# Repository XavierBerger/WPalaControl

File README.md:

# WPalaControl

**WPalaControl** is a device designed to control and monitor Fumis-based stoves using a D1 Mini.  
It allows you to power on/off, adjust the set point, change fan speeds, and retrieve status, alarms, and temperature data from your stove.  

It supports native HTTP requests which makes it fully compatible with all existing Palazzetti/Fumis home automation plugins/apps.  

It also integrates with MQTT to monitor/control your stove in a much more efficient way.  

## Stove Compatibility

WPalaControl is compatible with stoves using the Fumis Controller, which is used by many manufacturers, including:  
  
Palazzetti / Jotul / TurboFonte / Godin / Fonte Flamme / Invicta / Casatelli / Alpis / Faizen / HETA / ...

To determine if your stove is compatible with WPalaControl, look for the following Control Panel or Motherboard:  

## Home Automation compatibility

|  | [MQTT Integration](https://www.home-assistant.io/integrations/mqtt/) (autodiscovery) <br> Most options and fans control |  |
| ------------- | ------------- | ------------- |
|  | [Palazzetti Integration](https://www.home-assistant.io/integrations/palazzetti)<br> (2024.11 minimum) <br> Basic implementation for now |  |
|  | [Palazzetti plugin](https://www.jeedom.com/market/index.php?v=d&p=market_display&id=3104) |  |

## Make/Get your adapter

🔧 If you want to build it yourself, you can find all details here : [BUILD](BUILD.md) 🔧  

🛍️🚀 Otherwise, I'm producing some small batches and offering it ready-to-use here :  

## Connect

⚠️ **Before connecting, please check that you are using the correct cable**  
For Hardware V1.x: please use a **Crossed** cable  
For Hardware V2.x: please use a **Straight** cable  
_(Hardware version is written on the box and on the PCB)_

✅If your stove has an accessible RJ12 connector, simply connect the cable.  

🔍If not, you'll need an additional cable and a splitter.  
➡️ More details can be found in the [Splitter Cabling documentation](SPLITTERCABLING.md)

## First Boot

During the first Boot, the WPalaControl creates its own Wi-Fi network (AP mode)  

Firmware version **3.2.0 and higher**:  

- Network SSID : `WPalaControl`
- Password : `password`

Version **3.1.x and lower**:  

- Network SSID : `WirelessPalaControlXXXX`
- Password : `PasswordPalaControl`

You should be automatically redirected to the module page.  
If not, go to 👉 <http://wpalacontrol.local> 👈

## Configuration pages

### Status

Provides useful informations about the module and the stove.  
**The stove SN appears then followed, 1 minute later, by refreshed stove information**  

### Config

#### System

- **Reboot**: restart the module
- **Reboot in Rescue Mode**: restart the module with default configuration

#### WiFi

- **ssid & password**: IDs of your Wifi Network  
- **hostname**: name of ESP on the network  
- **IP, GW, NetMask, DNS1&2**: Fixed IP configuration  

#### PalaControl - Home Automation

- **Type**: enable/disable MQTT communication  
- **Upload Period**: set the refresh interval of stove information (in seconds)  
- **Hostname, Port, Username, Password**: MQTT server details (username and password are - optional)  
- **Base Topic**: prefix for WPalaControl topic structure  
- **MQTT Type**: defines MQTT topics and data structure:  
  - **Generic**: publish raw values under the base topic (e.g. "{baseTopic}/T1" = "*20.00*")
  - **Generic JSON**: publish values JSON to "category" topic under base topic (e.g. "{baseTopic}/TMPS" = "*{"INFO":{"CMD":"GET TMPS","RSP":"OK......*")
  - **Generic Categorized**: publish raw values to "category" topic under base topic (e.g. "{baseTopic}/TMPS/T1" = "*20.00*")
- **Home Assistant Discovery**: Enable/disable Home Assistant auto-discovery

### Firmware

Aallows you to flash a new firmware version directly from GitHub releases or using `WPalaControl.*.bin` or `WirelessPalaControl.*.bin` file:  
  
Ensure the module has Internet access and/or DNS configured if IP address is static

## Use it

### HTTP

Natively, HTTP GET request can be sent directly to the module.  

```
http://wpalacontrol.local/cgi-bin/sendmsg.lua?cmd={command}
```

### MQTT

Send commands via MQTT to `%BaseTopic%/cmd` topic once MQTT is configured.  
Execution result is:

- published following the configured MQTT Type
- published on `%BaseTopic%/result` in JSON format

Module connection status is published to `%BaseTopic%/connected`:

- 0: not connected
- 1: connected but no communication with the stove
- 2: module and stove connected

### Command List
  
- `GET+STDT`: get static data
- `GET+ALLS`: get all status data
- `GET+STAT`: get status of the stove⏲️
- `GET+TMPS`: get temperatures of the stove⏲️
- `GET+FAND`: get Fan values⏲️
- `GET+SETP`: get current Set Point (desired temperature)⏲️
- `GET+POWR`: get current power (1-5)⏲️
- `GET+CUNT`: get some counters
- `GET+CNTR`: get some counters (same as GET+CUNT)⏲️
- `GET+DPRS`: get delta pressure data⏲️
- `GET+TIME`: get stove clock data⏲️
- `GET+IOPT`: get IO ports status
- `GET+SERN`: get stove Serial Number
- `GET+MDVE`: get stove model and fw version
- `GET+CHRD`: get chrono data
- `GET+PARM+92`: get parameter (ex : 92=pellet type (1-3))
- `GET+HPAR+57`: get hidden parameter (ex : 57=% of pellet to feed for pellet type 3)
- `BKP+PARM+CSV`: get all parameters in a CSV file (HTTP only) ✨
- `BKP+PARM+JSON`: get all parameters in a JSON file (HTTP only) ✨
- `BKP+HPAR+CSV`: get all hidden parameters in a CSV file (HTTP only) ✨
- `BKP+HPAR+JSON`: get all hidden parameters in a JSON file (HTTP only) ✨
- `CMD+ON`: turn stove ON
- `CMD+OFF`: turn stove OFF
- `SET+POWR+3`: set power (1-5)
- `SET+PWRU`: increase power by 1 unit
- `SET+PWRD`: decrease power by 1 unit
- `SET+SETP+20`: set Set Point (desired temperature)
- `SET+STPF+19.8`: set Set Point with a 0.2° precision (depend of your stove model)✨
- `SET+STPU`: increase Set Point by 1 unit
- `SET+STPD`: decrease Set Point by 1 unit
- `SET+RFAN+7`: set Room Fan value (0-5;6=Max;7=Auto)
- `SET+FN2U`: increase Room Fan by 1 unit
- `SET+FN2D`: decrease Room Fan by 1 unit
- `SET+FN3L+0`: set Room Fan 3 value (0-5)
- `SET+FN4L+0`: set Room Fan 4 value (0-5)
- `SET+SLNT+0`: set Silent mode value (0-1)
- `SET+TIME+2023-12-28+19:42:00`: set stove Date and Time (2000-2099) (1-12) (1-31) (0-23) (0-59) (0-59)
- `SET+CSST+0`: set Chrono Status value (0-1)
- `SET+CSTH+2+18`: set Chrono Program Start Hour (1-6) (0-23)
- `SET+CSTM+2+30`: set Chrono Program Start Minute (1-6) (0-59)
- `SET+CSPH+2+22`: set Chrono Program Stop Hour (1-6) (0-23)
- `SET+CSPM+2+45`: set Chrono Program Stop Minute (1-6) (0-59)
- `SET+CSET+2+19`: set Chrono Program Set Point (1-6) (desired temperature)
- `SET+CDAY+7+3+6`: set Chrono Program for week day (Day-Mem-Prog) (1-7) (1-3) (1-6)
- `SET+CPRD+1+19+18+30+22+45`: set Chrono Program data (Prog-Temp-StartH-StartM-StopH-StopM) (1-6) (temperature) (0-23) (0-59) (0-23) (0-59)
- `SET+PARM+92+2`: set parameter 92 to value 2 (ex : 92=pellet type (1-3))
- `SET+HPAR+57+95`: set hidden parameter 57 to value 95 (ex : 57=% of pellet to feed for pellet type 3)

⏲️: Published automatically  
✨: WPalaControl specific commands

### Description

MQTT infos published every "Upload Period":

- `STATUS`: status of the stove
- `LSTATUS`: status of the stove
- `T1`, `T2`, `T3`, `T4`, `T5`: temperature of the stove
- `F1V`, `F2V`, `F2L`, `F2LF`, `F3L`, `F4L`: fan values (meaning depend of your stove model)
- `IGN`: ignition counter
- `IGNERRORS`: ignition error counter
- `POWERTIME`: total heating time (hour:minute)
- `HEATTIME`: ??? (hour:minute)
- `SERVICETIME`: heating time since last maintenance (hour:minute)
- `ONTIME`: time from last power ON (hour:minute)
- `OVERTMPERRORS`: overtemperature error counter
- `STOVE_DATETIME`: date of the stove
- `STOVE_WDAY`: week day of the stove
- `SETP`: current Set Point (desired temperature)
- `PQT`: wood pellet consumption
- `PWR`: current power (1-5)
- `FDR`: feeder
- `DP_TARGET`: delta pressure target
- `DP_PRESS`: actual delta pressure

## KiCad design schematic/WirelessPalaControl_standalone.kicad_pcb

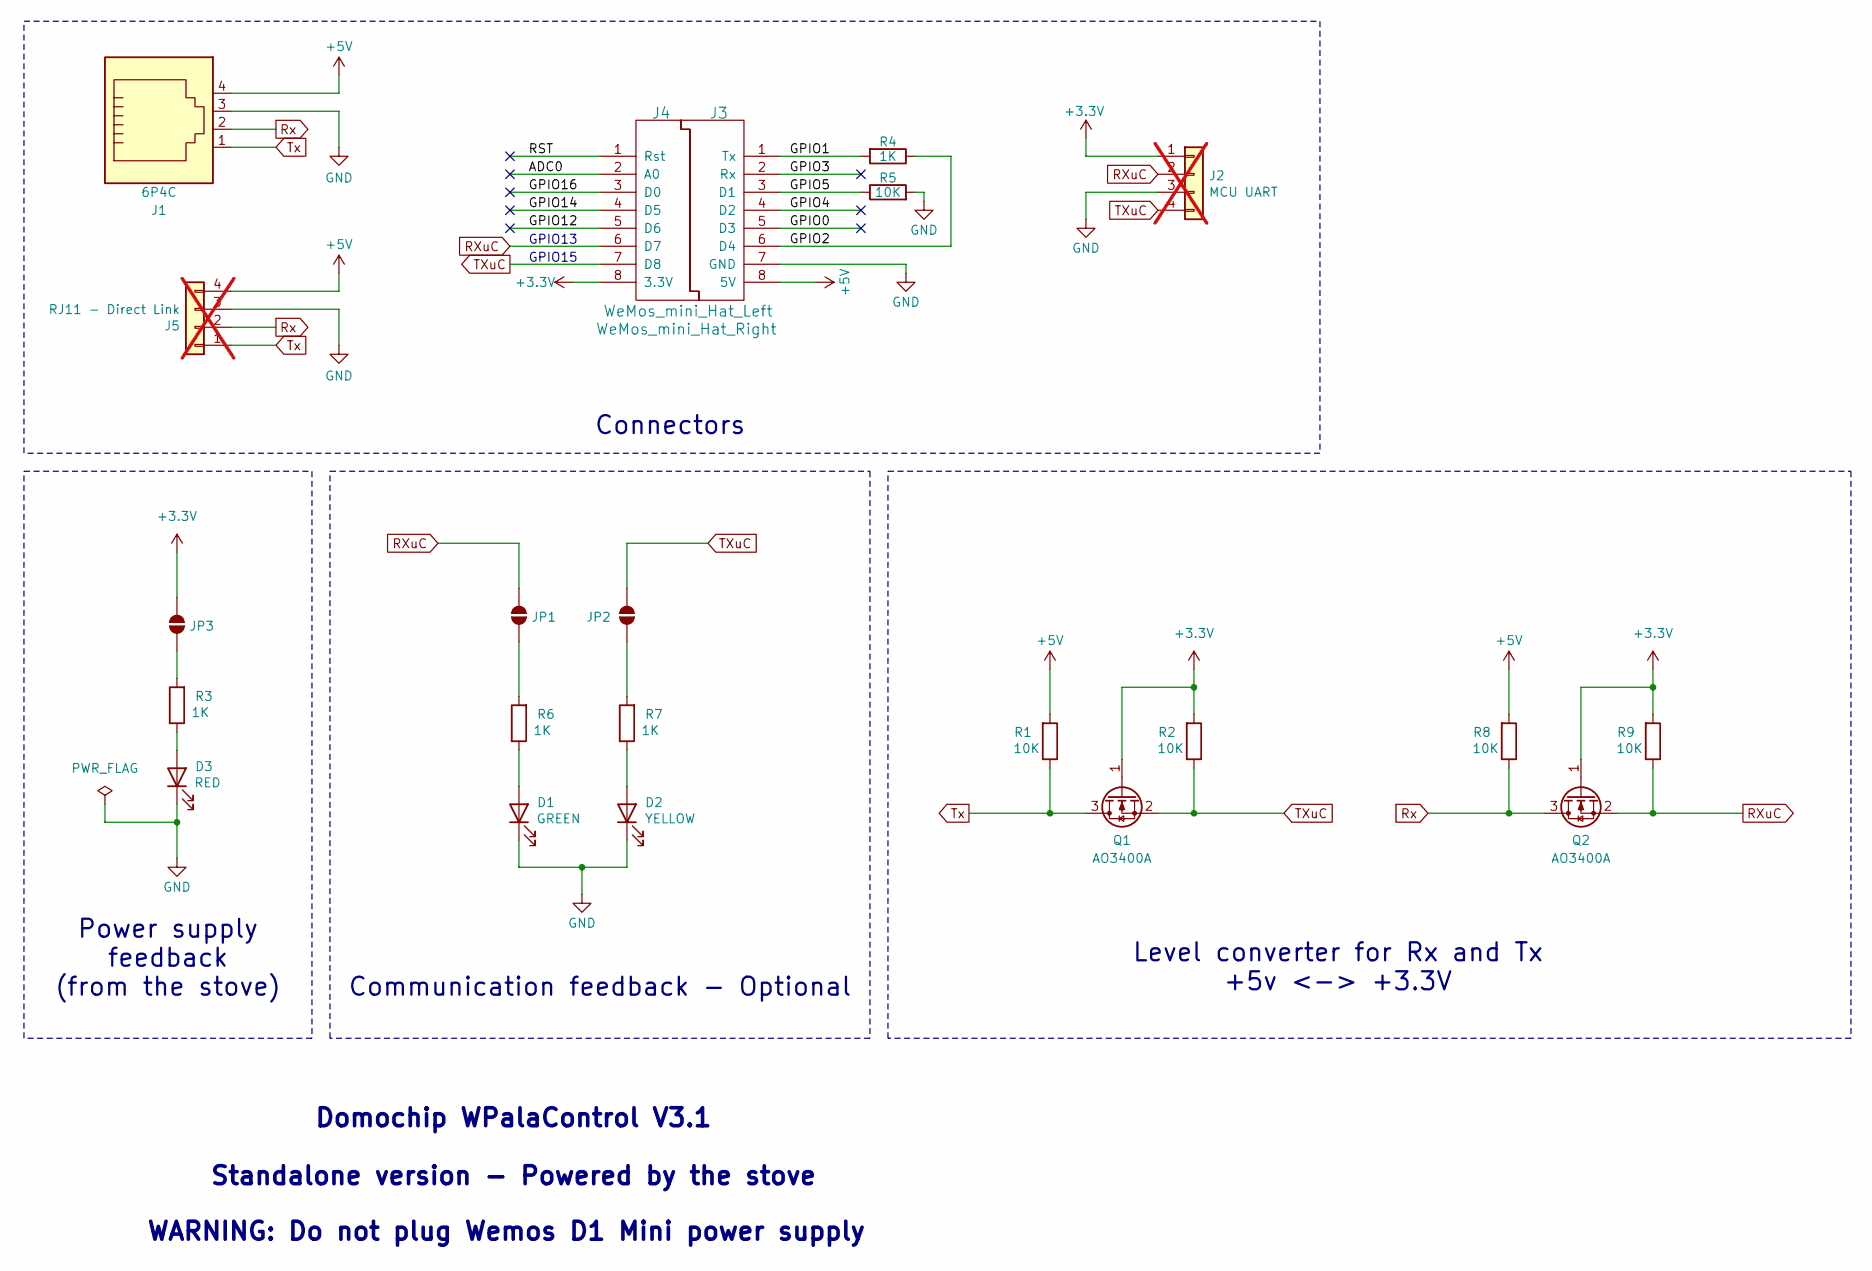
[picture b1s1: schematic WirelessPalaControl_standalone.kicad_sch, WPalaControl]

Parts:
D1: GREEN; LED_0805_2012Metric_Pad1.15x1.40mm_HandSolder; LCSC C2297
D2: YELLOW; LED_0805_2012Metric_Pad1.15x1.40mm_HandSolder; LCSC C2296
D3: RED; LED_0805_2012Metric_Pad1.15x1.40mm_HandSolder; LCSC C84256
J1: 6P4C; Ali_RJ11; LCSC C189749
J2: MCU UART; PinHeader_1x04_P2.54mm_Vertical; not fitted
J3: WeMos_mini_Hat_Left; PinSocket_1x08_P2.54mm_Vertical; LCSC C7509515
J4: WeMos_mini_Hat_Right; WeMos_D1_mini_Hat_Right; LCSC C7509515
J5: RJ11 - Direct Link; PinHeader_1x04_P2.54mm_Vertical; not fitted
JP1, JP2, JP3: SolderJumper_2_Open; SolderJumper-2_P1.3mm_Open_TrianglePad1.0x1.5mm
Q1, Q2: AO3400A; SOT-23
R1, R2, R5, R8, R9: 10K; R_0805_2012Metric_Pad1.20x1.40mm_HandSolder; LCSC C17414
R3, R4, R6, R7: 1K; R_0805_2012Metric_Pad1.20x1.40mm_HandSolder; LCSC C17513

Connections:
+3.3V: J2.1, J4.8 (3.3V), JP3.1 (A), Q1.1 (G), Q2.1 (G), R2.2, R9.2
+5V: J1.4, J3.8 (5V), J5.4, R1.2, R8.2
/ADC0: J4.2 (A0)
/GPIO0: J3.5 (D3)
/GPIO1: J3.1 (Tx), R4.2
/GPIO2: J3.6 (D4), R4.1
/GPIO3: J3.2 (Rx)
/GPIO4: J3.4 (D2)
/GPIO5: J3.3 (D1), R5.1
/GPIO12: J4.5 (D6)
/GPIO14: J4.4 (D5)
/GPIO16: J4.3 (D0)
/RST: J4.1 (Rst)
GND: D1.1 (K), D2.1 (K), D3.1 (K), J1.3, J2.3, J3.7 (GND), J5.3, R5.2
unnamed: D1.2 (A), R6.1
unnamed: D2.2 (A), R7.1
unnamed: D3.2 (A), R3.1
unnamed: JP1.2 (B), R6.2
unnamed: JP2.2 (B), R7.2
unnamed: JP3.2 (B), R3.2
RXuC: J2.2, J4.6 (D7), JP1.1 (A), Q2.2 (S), R9.1
Rx: J1.2, J5.2, Q2.3 (D), R8.1
TXuC: J2.4, J4.7 (D8), JP2.1 (A), Q1.2 (S), R2.1
Tx: J1.1, J5.1, Q1.3 (D), R1.1

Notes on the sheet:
Domochip WPalaControl V3.1 Standalone version - Powered by the stove
Power supply feedback (from the stove)
Communication feedback - Optional
WARNING: Do not plug Wemos D1 Mini power supply
GPIO15
Level converter for Rx and Tx +5v <-> +3.3V
Connectors
GPIO13

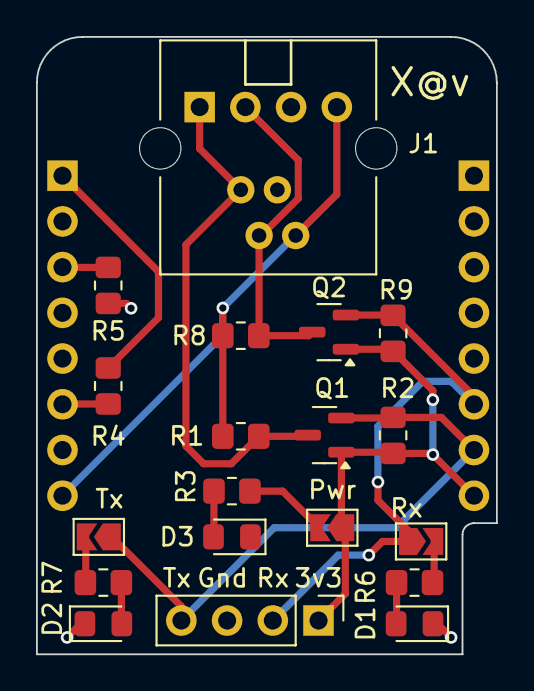
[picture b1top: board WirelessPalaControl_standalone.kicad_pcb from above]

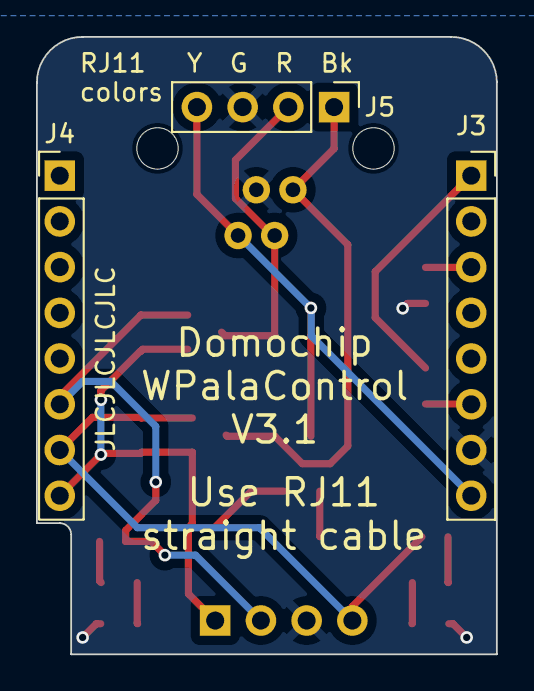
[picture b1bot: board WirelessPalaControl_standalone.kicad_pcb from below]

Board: 2 copper layers, 25.6 x 34.3 mm, 22 parts (3 on the bottom side), 16 nets.

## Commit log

2024-10-25 Adapt code for Base 2.4.0
2024-10-28 Adapt code for Base 2.4.2
2024-10-28 Save RAM #1
2024-10-28 Comment
2024-10-29 Rename some functions
2024-10-29 Use new MQTTMan getStateString() method
2024-10-29 Adapt code for Base 2.4.5
2024-10-29 Adapt code for Base 2.4.7
2024-10-29 Adapt code for Base 2.4.8
2024-10-30 Adapt code for Base 2.4.10
2024-10-30 Adapt code for Base 2.4.11
2024-10-30 Adapt code for Base 2.4.12
2024-10-31 Adapt code for Base 2.4.14
2024-10-31 Fix lib version problem
2024-11-01 Simplify default AP password
2024-11-01 Fix default AP password
2024-11-01 Adapt code for Base 2.4.16
2024-11-01 Adapt code for Base 2.4.18
2024-11-01 Add Home Assistant update entity (#55)
    * Add Update publish Ticker
    * Add Update publish in appRun
    * Add Update publish in appInit
    * Add mqttPublishUpdate method
    * Add subscription to update/install topic
    * Improve mqttConnectedCallback block distinction
2024-11-01 Bump version to 3.2.0
2024-11-01 Fix EventSourceServer initialization
2024-11-03 Use new Palazzetti lib version
2024-11-03 Bump version to 3.2.1
2024-11-03 Fix new Palazzetti lib usage
2024-11-04 Bump version to 3.2.2
2024-11-04 3.2.x documentation (#56)
    * Raise Home Assistant min version to 2021.11
    * Add SPLITTERCABLING.md
    * Update README.md
    * Update cabling.png
    * Update status.png
    * Update screenshots
2024-11-07 Use newest Palazzetti lib
2024-11-08 Hass 2024.11 update progress (#57)
    * Implement new Home Assistant Update progress
    * Update README.md
2024-11-14 Improve Home Assistant tempertaure entities for Hydro stove (#59)
    * Add isFluidType and update home assistant params
    * FLUID can be 0,1 or 2 so not really a boolean
    * Quick fix for min/max until UI research
    * Add UICONFIG and isHydroType
    * Rollback duplication of code
    * Determine the Main temperature sensor
2024-11-14 Reduce setpoint slider limit from 17 to 15
2024-11-14 Bump version to 3.3.0
2024-11-16 Add climate (#62)
    * Group FlashString lists
    * More usefull variables grouped
    * Use new tempProbeTopicListArray variable
    * Add Thermostat (climate) entity
    * Add Power command to Thermostat
    * Add temperature command topic
2024-11-16 Improve code readability
2024-11-16 Add publishJson helper function
2024-11-16 Add prepareEntityTopic helper function
2024-11-16 remove unused payload variable
2024-11-16 Add T3 entity (disabled by default)
2024-11-16 Increase max mqtt buffer for climate
2024-11-16 Use Stove limits in setPoint slider now
2024-11-16 Add Service Time Counter entity
2024-11-16 Adding Feeder entity
2024-11-16 Fix Fan mode list
2024-11-17 Add differential pressure and dp target entities
2024-11-17 Fix missing temperature sensor suffix
2024-11-17 Add missing publish for service time
2024-11-17 Rounding diffrential pressures
2024-11-17 Remove device_class for service time counter for better display
2024-11-17 Fix service time counter parsing
2024-11-17 Fix topic for Room/Return/Tank autodiscover topic
2024-11-17 Bump version to 3.4.0
2024-11-17 Adjust climate max vaue for air setpoint
2024-11-17 Update images
2024-11-24 New Hardware Version (V2.0) (#65)
    * Add hw version detection
    * New PCB version
    * Implement Hardware detection
    * Do Not Place J2
    * New box
    * Update box
2024-11-24 Bump version to 3.5.0
2025-09-18 Add "Set Time" button to Home Assistant autodiscover
2025-09-19 feat(hw): cleanup PCB
2025-09-19 feat(hw): Update BOM with JLCPCB part numbers
2025-09-19 feat(hw): Cleanup schematic
2025-09-19 feat(hw): Redesign standalone version with optionnal LED activation
2025-09-19 feat(hw): Add Standalone version of PCB
2025-09-19 feat(hw): Add connector to directly solder a RJ11 cable
2025-09-26 feat(hw): draft - Use D1 mini LDO
